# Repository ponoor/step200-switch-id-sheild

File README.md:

# step200-switch-id-sheild
A small PCB design for adding home switch inputs and a dip switch

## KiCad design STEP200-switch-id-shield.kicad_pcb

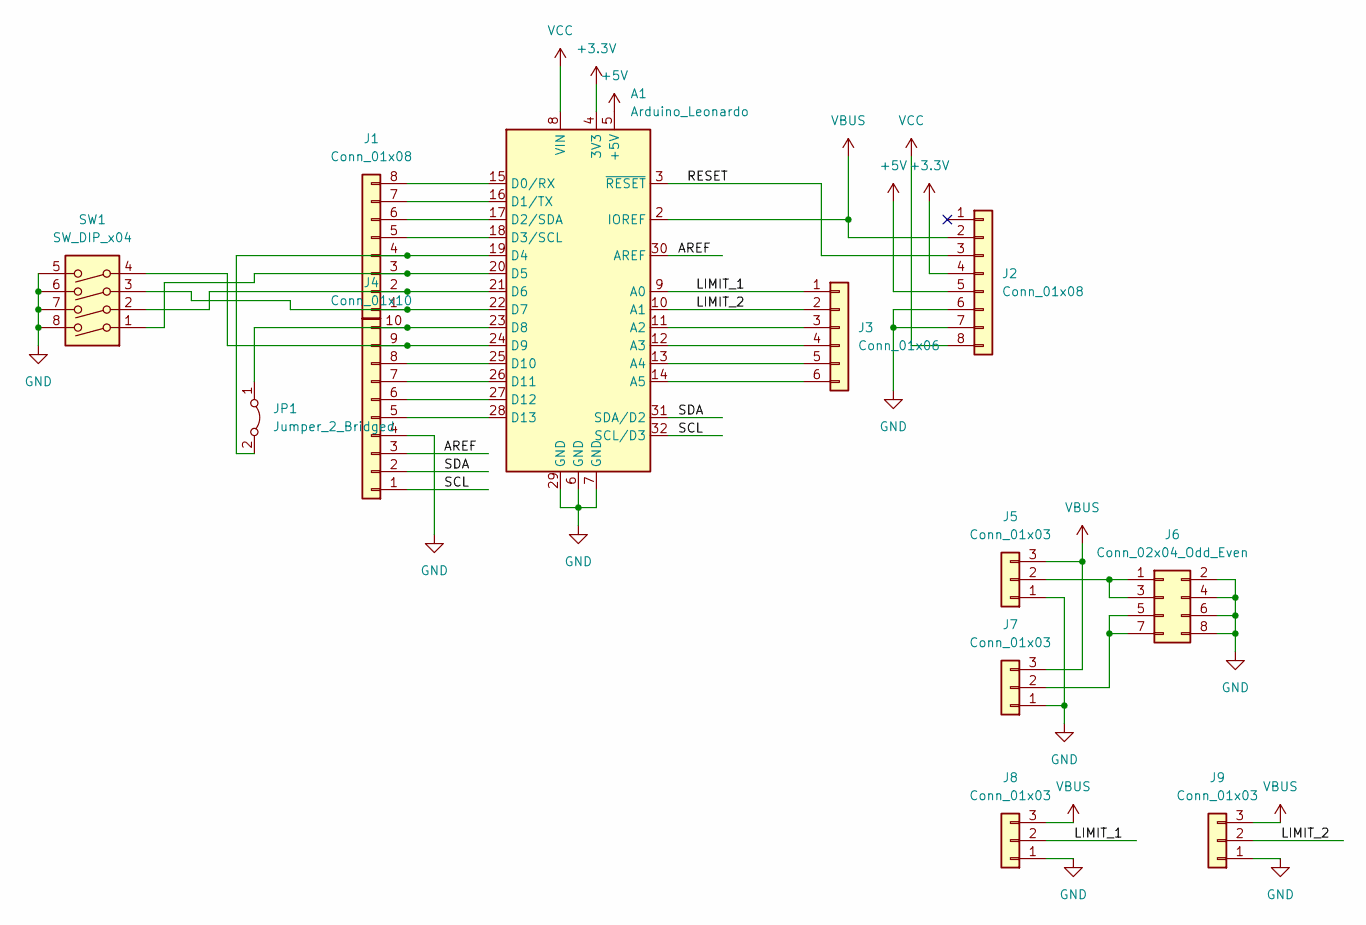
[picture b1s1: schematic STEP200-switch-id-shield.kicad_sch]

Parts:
A1: Arduino_Leonardo; Arduino_UNO_R3
J1, J2: Conn_01x08; PinSocket_1x08_P2.54mm_Vertical
J3: Conn_01x06; PinSocket_1x06_P2.54mm_Vertical
J4: Conn_01x10; PinSocket_1x10_P2.54mm_Vertical
J5, J7, J8, J9: Conn_01x03; JST_XA_B03B-XASK-1_1x03_P2.50mm_Vertical
J6: Conn_02x04_Odd_Even; PinSocket_2x04_P2.54mm_Vertical
JP1: Jumper_2_Bridged; SolderJumper-2_P1.3mm_Bridged_Pad1.0x1.5mm
SW1: SW_DIP_x04; SW_DIP_SPSTx04_Slide_9.78x12.34mm_W7.62mm_P2.54mm

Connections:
+3.3V: A1.4 (3V3), J2.4
+5V: A1.5 (+5V), J2.5
/AREF: A1.30 (AREF), J4.3
/LIMIT_1: A1.9 (A0), J3.1, J8.2
/LIMIT_2: A1.10 (A1), J3.2, J9.2
/RESET: A1.3 (~RESET), J2.3
/SCL: A1.32 (SCL/D3), J4.1
/SDA: A1.31 (SDA/D2), J4.2
GND: A1.6 (GND), A1.7 (GND), A1.29 (GND), J2.6, J2.7, J4.4, J5.1, J6.2, J6.4, J6.6, J6.8, J7.1, J8.1, J9.1, SW1.5, SW1.6, SW1.7, SW1.8
unnamed: A1.11 (A2), J3.3
unnamed: A1.12 (A3), J3.4
unnamed: A1.13 (A4), J3.5
unnamed: A1.14 (A5), J3.6
unnamed: A1.15 (D0/RX), J1.8
unnamed: A1.16 (D1/TX), J1.7
unnamed: A1.17 (D2/SDA), J1.6
unnamed: A1.18 (D3/SCL), J1.5
unnamed: A1.19 (D4), J1.4, JP1.2 (B)
unnamed: A1.20 (D5), J1.3, SW1.1
unnamed: A1.21 (D6), J1.2, SW1.2
unnamed: A1.22 (D7), J1.1, SW1.3
unnamed: A1.23 (D8), J4.10, JP1.1 (A)
unnamed: A1.24 (D9), J4.9, SW1.4
unnamed: A1.25 (D10), J4.8
unnamed: A1.26 (D11), J4.7
unnamed: A1.27 (D12), J4.6
unnamed: A1.28 (D13), J4.5
unnamed: J5.2, J6.1, J6.3
unnamed: J6.5, J6.7, J7.2
VBUS: A1.2 (IOREF), J2.2, J5.3, J7.3, J8.3, J9.3
VCC: A1.8 (VIN), J2.8

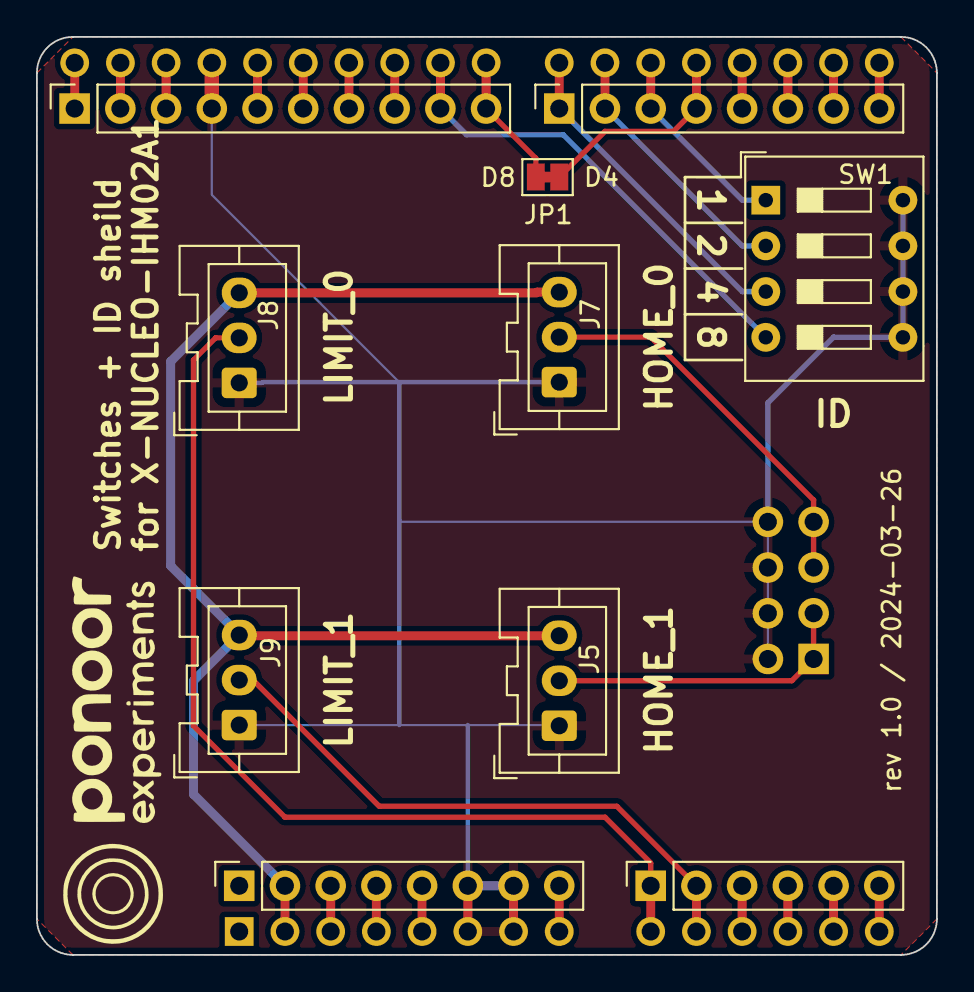
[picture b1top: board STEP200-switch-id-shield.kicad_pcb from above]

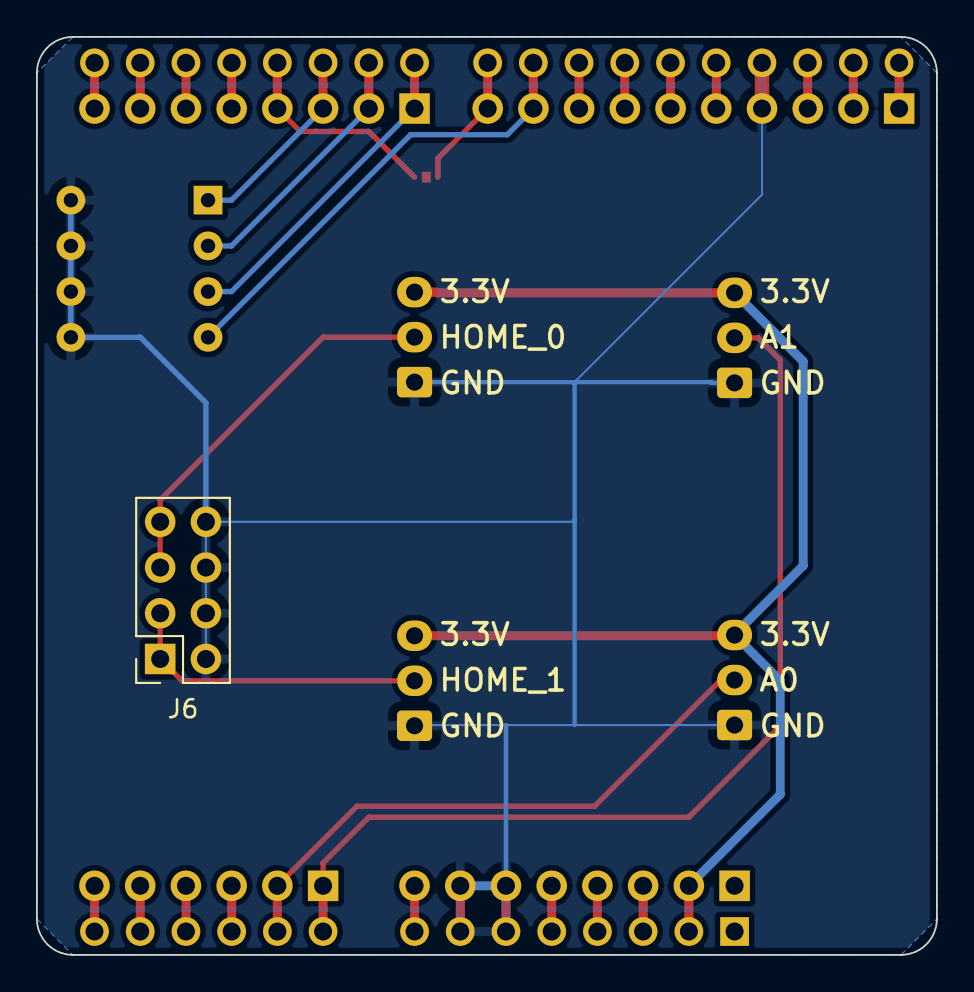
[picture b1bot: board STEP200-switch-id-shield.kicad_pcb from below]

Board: 2 copper layers, 50.0 x 51.0 mm, 12 parts (2 on the bottom side), 31 nets.

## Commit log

2024-03-26 board design
